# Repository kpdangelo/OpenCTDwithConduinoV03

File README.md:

# OpenCTDwithConduinoV03

This has drift issues, see https://github.com/kpdangelo/OpenCTD-Conduino-K1.0

This is version 3 of my conduino implementation
The circuit more closely follows the Analog Devices app note, CN-0217, in an attempt to mitigate the drift I was seeing in the Conduino reading with versions 1 and 2.
Namely, the AC coupling capacitors in series with the USB electrodes were taken studied, and a SPDT analog mux was added to swap the electrodes for each measurement in an attempt to see if there was biasing going on of the electrodes.
All fairly inconclusive at this time.

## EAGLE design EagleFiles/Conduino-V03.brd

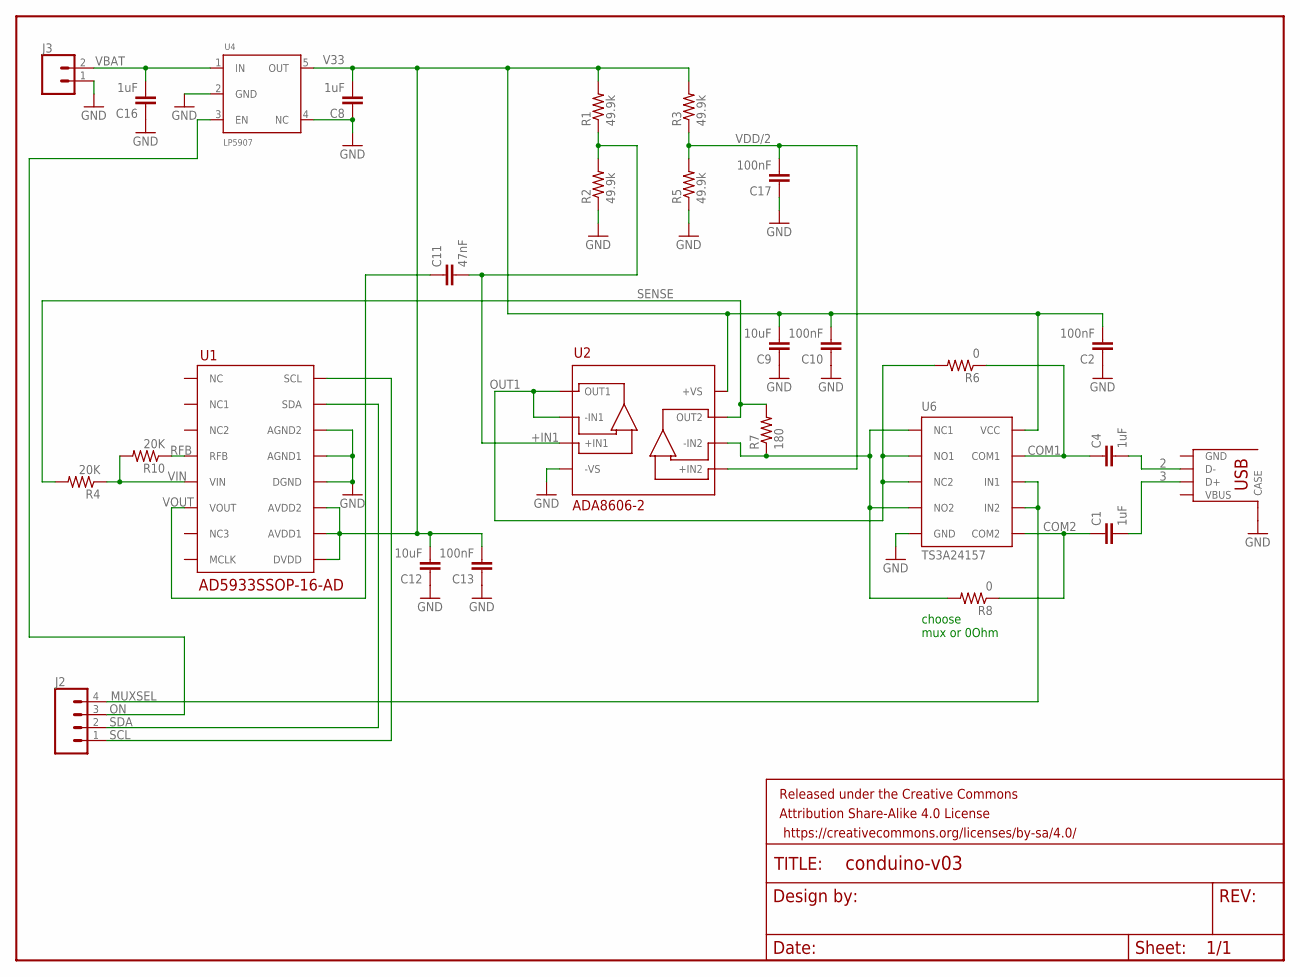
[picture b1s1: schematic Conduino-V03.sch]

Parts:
C1, C4, C8, C16: 1uF; 0603-CAP
C2, C10, C13, C17: 100nF; 0603-CAP
C9, C12: 10uF; 0603-CAP
C11: 47nF; 0603-CAP
FRAME1: FRAME-LETTER; CREATIVE_COMMONS
J1: USBA-SIDE
J2: CONN_041X04_NO_SILK; 1X04_NO_SILK
J3: CONN_021X02_NO_SILK; 1X02_NO_SILK
R1, R2, R3, R5: 49.9k; 0603-RES
R4, R10: 20K; 0603-RES
R6, R8: 0; 0603-RES
R7: 180; 0603-RES
U1: AD5933SSOP-16-AD; SSOP-16-AD
U2: ADA8606-2; SOIC_N
U4: LP5907; SOT23-5L
U6: TS3A24157; VSSOP-10

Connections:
2: C4.2, J1.P$2 (D-)
3: C1.2, J1.P$3 (D+)
+IN1: C11.2, R1.1, R2.2, U2.P$3 (+IN1)
-IN2: R7.1, R8.2, U2.P$6 (-IN2), U6.P$1 (NC1), U6.P$4 (NO2)
COM1: C4.1, R6.1, U6.P$9 (COM1)
COM2: C1.1, R8.1, U6.P$6 (COM2)
GND: C2.1, C8.1, C9.1, C10.1, C12.1, C13.1, C16.1, C17.1, J1.P$5 (CASE), J1.P$6 (CASE), J3.1, R2.1, R5.1, U1.P$12 (DGND), U1.P$13 (AGND1), U1.P$14 (AGND2), U2.P$4 (-VS), U4.2 (GND), U4.4 (NC), U6.P$5 (GND)
MUXSEL: J2.4, U6.P$7 (IN2), U6.P$8 (IN1)
ON: J2.3, U4.3 (EN)
OUT1: R6.2, U2.P$1 (OUT1), U2.P$2 (-IN1), U6.P$2 (NO1), U6.P$3 (NC2)
RFB: R10.1, U1.P$4 (RFB)
SCL: J2.1, U1.P$16 (SCL)
SDA: J2.2, U1.P$15 (SDA)
SENSE: R4.2, R7.2, U2.P$7 (OUT2)
V33: C2.2, C8.2, C9.2, C10.2, C12.2, C13.2, R1.2, R3.2, U1.P$9 (DVDD), U1.P$10 (AVDD1), U1.P$11 (AVDD2), U2.P$8 (+VS), U4.5 (OUT), U6.P$10 (VCC)
VBAT: C16.2, J3.2, U4.1 (IN)
VDD/2: C17.2, R3.1, R5.2, U2.P$5 (+IN2)
VIN: R4.1, R10.2, U1.P$5 (VIN)
VOUT: C11.1, U1.P$6 (VOUT)

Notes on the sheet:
choose mux or 0Ohm

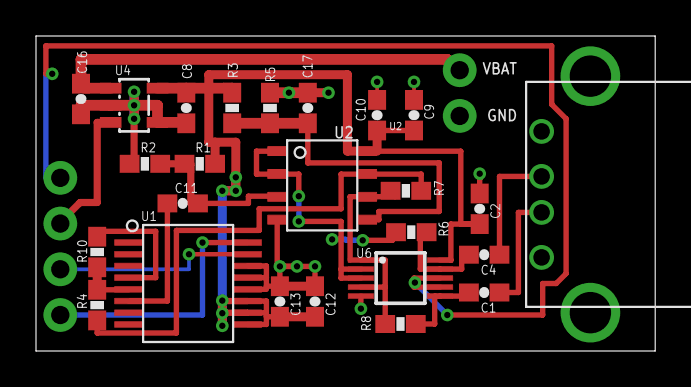
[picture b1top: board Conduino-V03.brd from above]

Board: 2 copper layers, 34.4 x 17.5 mm, 28 parts (0 on the bottom side), 19 nets.

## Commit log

2018-06-27 Create temp

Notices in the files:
parts and their libraries:
SparkFun-Aesthetics: Licensing: Creative Commons ShareAlike 4.0 International - https://creativecommons.org/licenses/by-sa/4.0
SparkFun-Aesthetics: Released under the Creative Commons
SparkFun-Aesthetics: https://creativecommons.org/licenses/by-sa/4.0
